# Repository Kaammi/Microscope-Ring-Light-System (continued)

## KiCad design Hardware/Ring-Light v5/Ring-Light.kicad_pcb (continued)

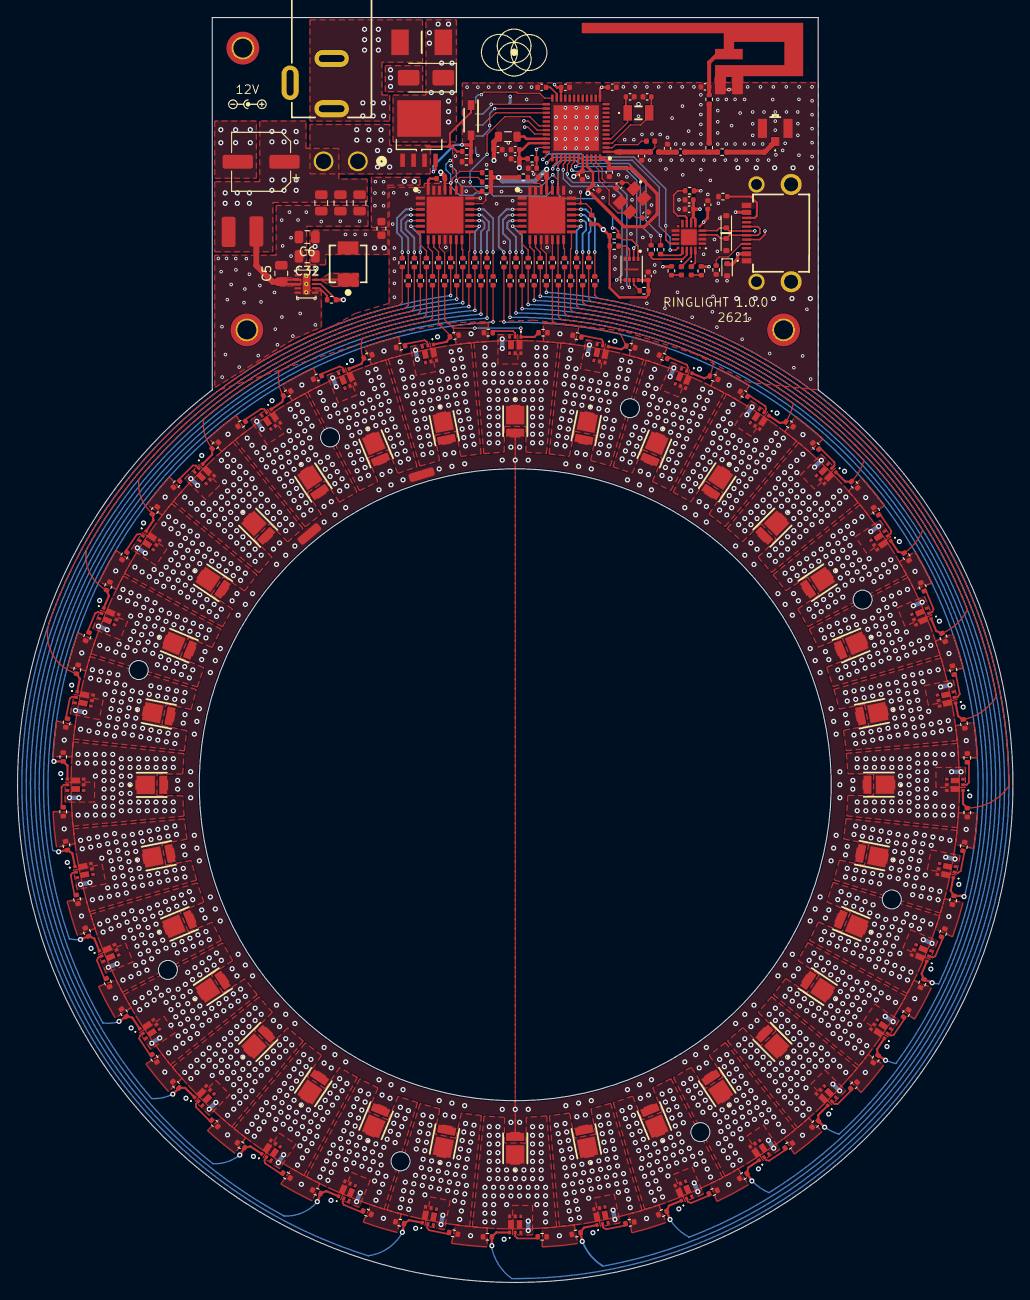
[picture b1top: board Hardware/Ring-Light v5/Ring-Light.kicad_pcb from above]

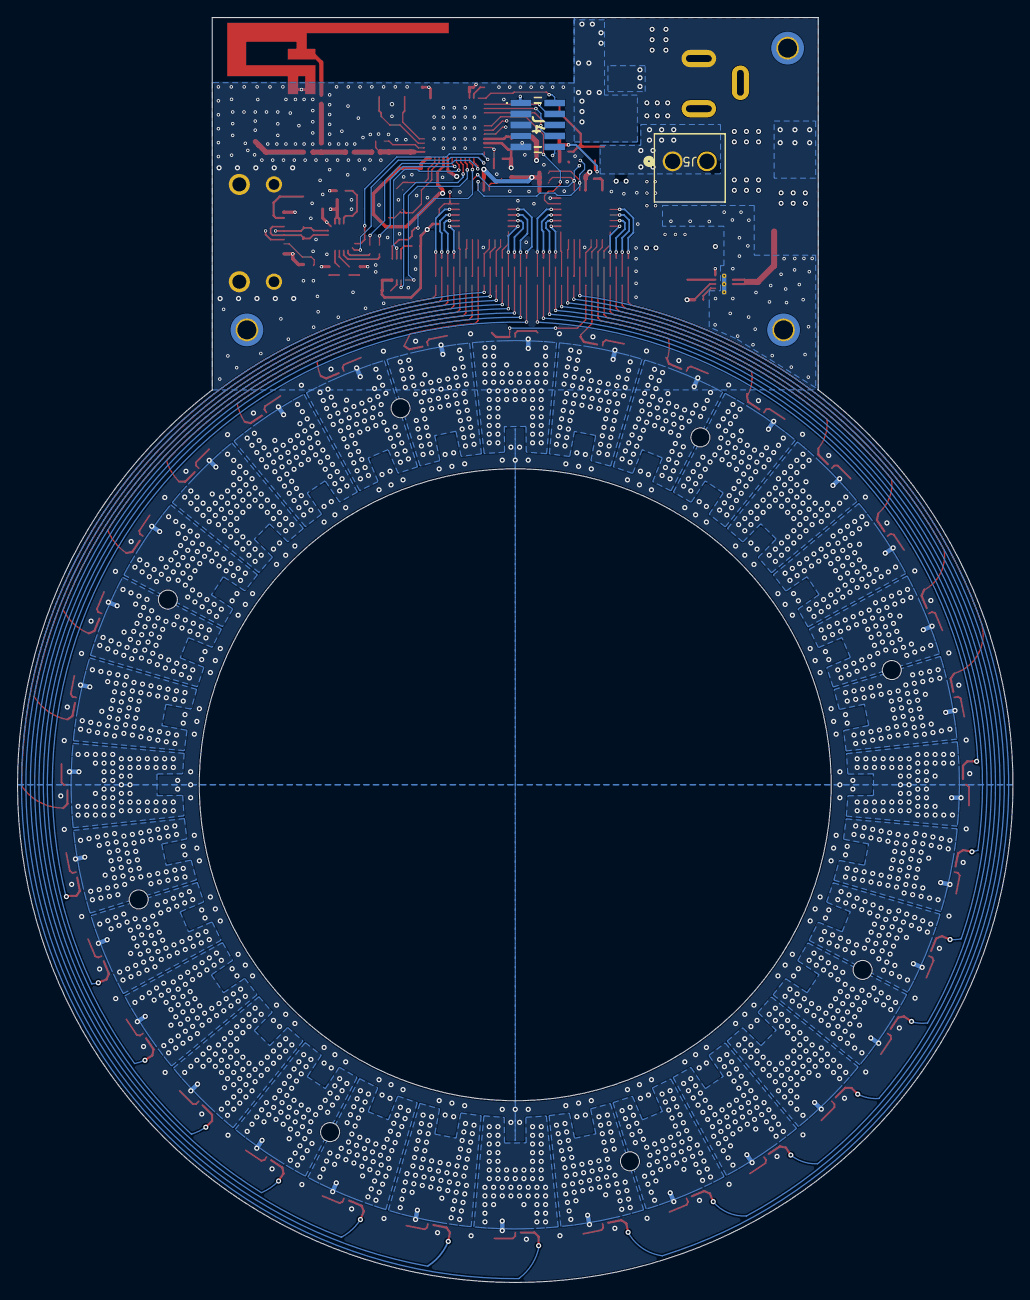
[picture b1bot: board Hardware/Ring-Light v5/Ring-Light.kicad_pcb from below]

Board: 4 copper layers, 115.0 x 146.1 mm, 252 parts (2 on the bottom side), 184 nets.

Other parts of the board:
MH1, MH2, MH3, MH4, MH5, MH5#2, MH6, MH7: MountingHole_2.2mm_M2

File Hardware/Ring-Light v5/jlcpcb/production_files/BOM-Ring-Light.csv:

Comment,Designator,Footprint,LCSC,Quantity
0,"R105,R106,R112,R113",R_0402_1005Metric,C17168,4
1.2pF,"C14,C27",C_0402_1005Metric,C72135,2
100,"R66,R67,R68,R69,R70,R71,R72,R73,R74,R75,R76,R77,R78,R79,R80,R81,R83,R84,R85,R86,R87,R88,R89,R90,R91,R92,R93,R94,R95,R96,R97,R98",R_0402_1005Metric,C25076,32
100k,"R1,R104,R11,R116,R117,R13,R15,R17,R19,R21,R23,R25,R27,R29,R3,R31,R33,R35,R37,R39,R41,R43,R45,R47,R49,R5,R51,R53,R55,R57,R59,R61,R63,R7,R9,R99",R_0402_1005Metric,C25741,36
100nF,"C1,C10,C12,C13,C15,C16,C17,C19,C2,C31,C7,C8",C_0402_1005Metric,C307331,12
1017457000B11LF,J2,1017457000B11LF,C22466645,1
10k,"R101,R108,R109,R118,R119,R65,R82",R_0402_1005Metric,C25744,7
10uF,"C11,C18",C_0402_1005Metric,C15525,2
10uF,C9,C_0805_2012Metric,C15850,1
10uH,L2,L_0805_2012Metric,C1046,1
12pF,"C22,C24,C25,C28,C29",C_0402_1005Metric,C1547,5
1k,"R100,R102,R103,R107,R114",R_0402_1005Metric,C11702,5
1uF,C30,C_0805_2012Metric,C28323,1
1uF,"C20,C21",C_0402_1005Metric,C52923,2
2.2k,R110,R_0402_1005Metric,C25879,1
2.2uF,C5,C_0805_2012Metric,C377773,1
2002112100010C4LF,J4,2002112100010C4LF,C150517,1
22uF,"C32,C6",C_0805_2012Metric,C45783,2
24MHz,Y2,TSX-3225,C2650460,1
32.768kHz,Y1,FC135327680KAAG0,C7275970,1
4.7uF,C26,C_0805_2012Metric,C1779,1
640445-2,J5,CONN2_640445-2_TEC,C86497,1
9.09,"R10,R12,R14,R16,R18,R2,R20,R22,R24,R26,R28,R30,R32,R34,R36,R38,R4,R40,R42,R44,R46,R48,R50,R52,R54,R56,R58,R6,R60,R62,R64,R8",R_0402_1005Metric,C166420,32
BLM18HE152SN1,FL1,L_0603_1608Metric,C82155,1
CP2102N-A02-GQFN20R,U37,CP2102NA02GQFN20,C969913,1
LED,"D1,D10,D11,D12,D13,D14,D15,D16,D17,D18,D19,D2,D20,D21,D22,D23,D24,D25,D26,D27,D28,D29,D3,D30,D31,D32,D4,D5,D6,D7,D8,D9",GWJTLRS1EMLVL5XX531,C2830571,32
MMSZ5242BT1G,D39,SOD3716X135N,C82050,1
NCR321PASX,"U1,U10,U11,U12,U13,U14,U15,U16,U17,U18,U19,U2,U20,U21,U22,U23,U24,U25,U26,U27,U28,U29,U3,U30,U31,U32,U4,U5,U6,U7,U8,U9",NCR321PASX,C3190647,32
"PCA9685BS,118","U33,U34",QFN65P600X600X100-29N-D,C5191634,2
SMAJ15A,D38,D_SMA,C132950,1
SQJ415EP-T1_GE3,Q1,SOT_SQJ415EP_VIS,C6495662,1
TPD1E10B06DPYR,"D33,D34,D35",D_SOD-523,C48260,3
TPS62177DQC,U36,WSON-10-1EP_2x3mm_P0.5mm_EP0.84x2.4mm_ThermalVias,C91241,1
U.FL-R-SMT-1_80,J3,UFLRSMT180,C88374,1
VLMY1500-GS08,"D36,D37",LED_0402_1005Metric,C511605,2
W25X40CLUXIG_TR,U38,PSON50P300X200X60-9N,C401661,1
100uF,C3,CP_Elec_6.3x7.7,,1
Fuse,F1,FUSC6127X294N,,1
694106301002,J1,694106301002,,1
Conn_01x01,J6,,,1
Conn_01x01,J7,,,1
Conn_01x01,J8,,,1
Conn_01x01,J9,,,1
10uH,L1,WE-LHMI_4020,,1
2nH,L3,L_0402_1005Metric,,1
15nH,L7,L_0402_1005Metric,,1
pad,REF**,pad,,1

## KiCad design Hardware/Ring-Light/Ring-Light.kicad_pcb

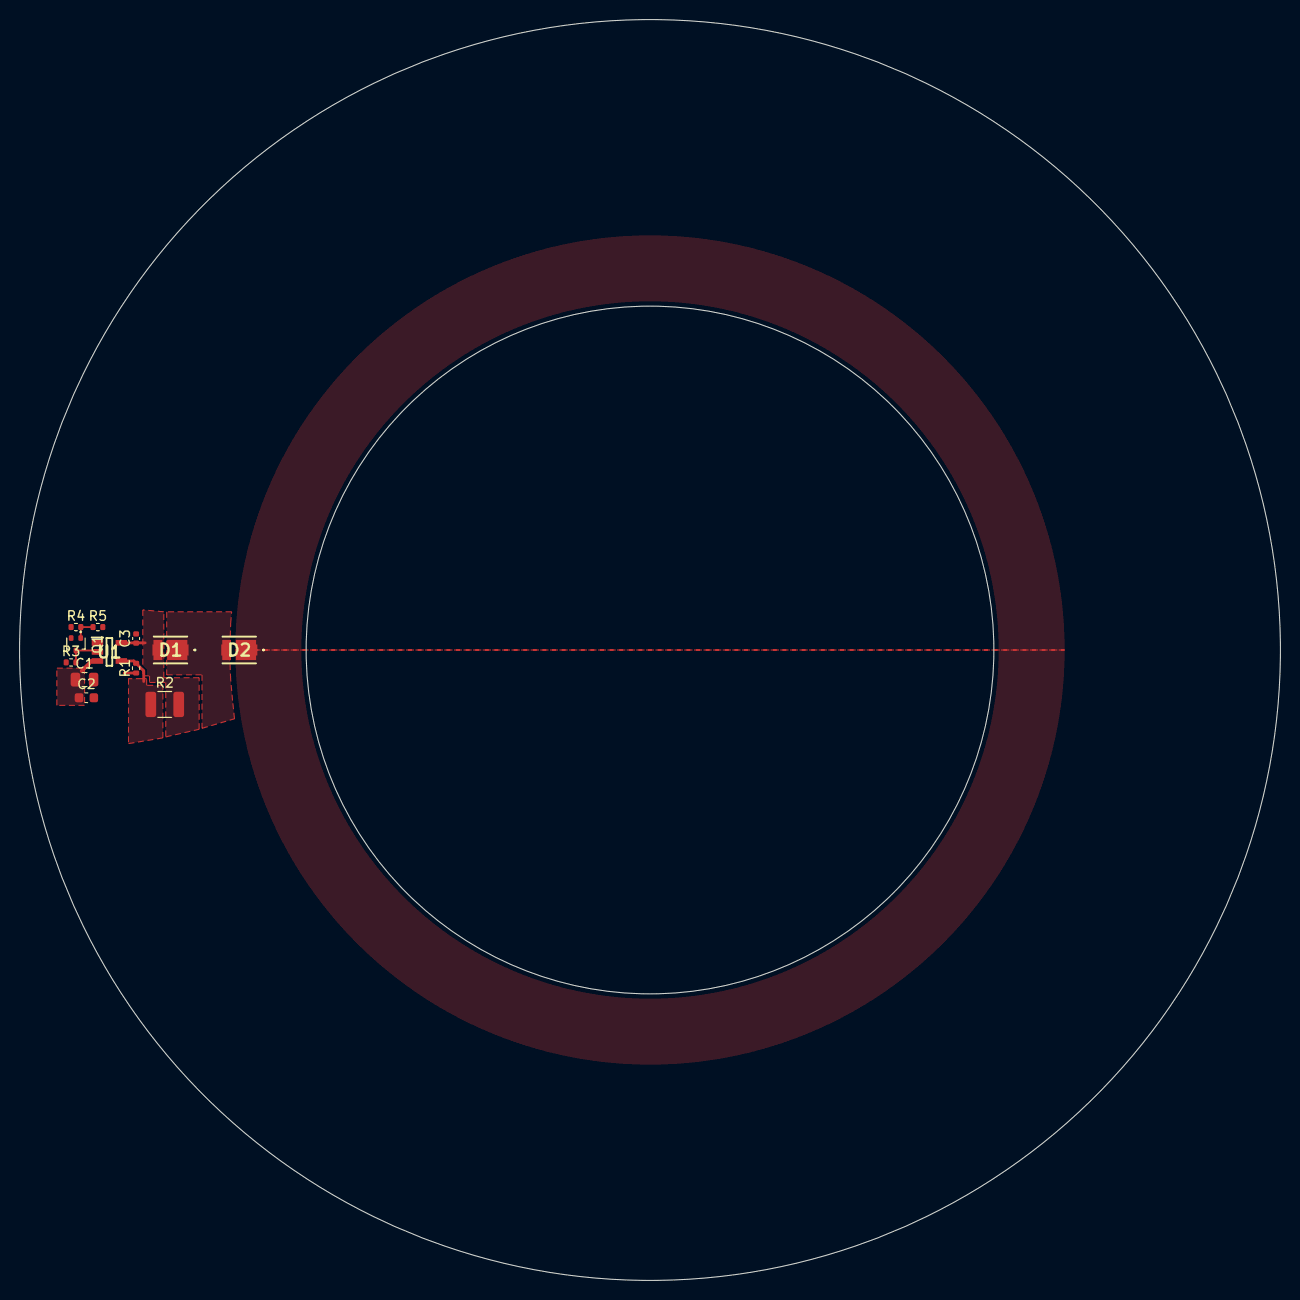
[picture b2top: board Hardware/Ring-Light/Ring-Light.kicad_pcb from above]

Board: 4 copper layers, 132.0 x 132.0 mm, 12 parts (0 on the bottom side), 7 nets.

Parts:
C1: 1uF; C_0805_2012Metric
C2: 0.1uF; C_0603_1608Metric
C3: 10nF; C_0402_1005Metric
D1, D2: LED; GWJTLRS1EMLVL5XX531
Q1: MMBT3904; SOT-416
R1: 1; R_0402_1005Metric
R2: 80.6; R_1210_3225Metric
R3: 1k; R_0402_1005Metric
R4, R5: 10k; R_0402_1005Metric
U1: TPS92612QDBVRQ1; SOT95P280X145-5N

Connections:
+12V: C1.1, C2.1, R1.1, U1.3 (SUPPLY)
/B1: Q1.1 (B), R4.2, R5.1
/IN1: R1.2, R2.1, U1.4 (IN)
/LED1: D1.1 (K), D1.2 (K), D2.3 (A), D2.4 (A)
/OUT1: C3.1, D1.3 (A), D1.4 (A), R2.2, U1.5 (OUT)
/PWM1: Q1.3 (C), R3.2, U1.2 (PWM)
GND: C1.2, C2.2, C3.2, D2.1 (K), D2.2 (K), Q1.2 (E), R5.2, U1.1 (GND)

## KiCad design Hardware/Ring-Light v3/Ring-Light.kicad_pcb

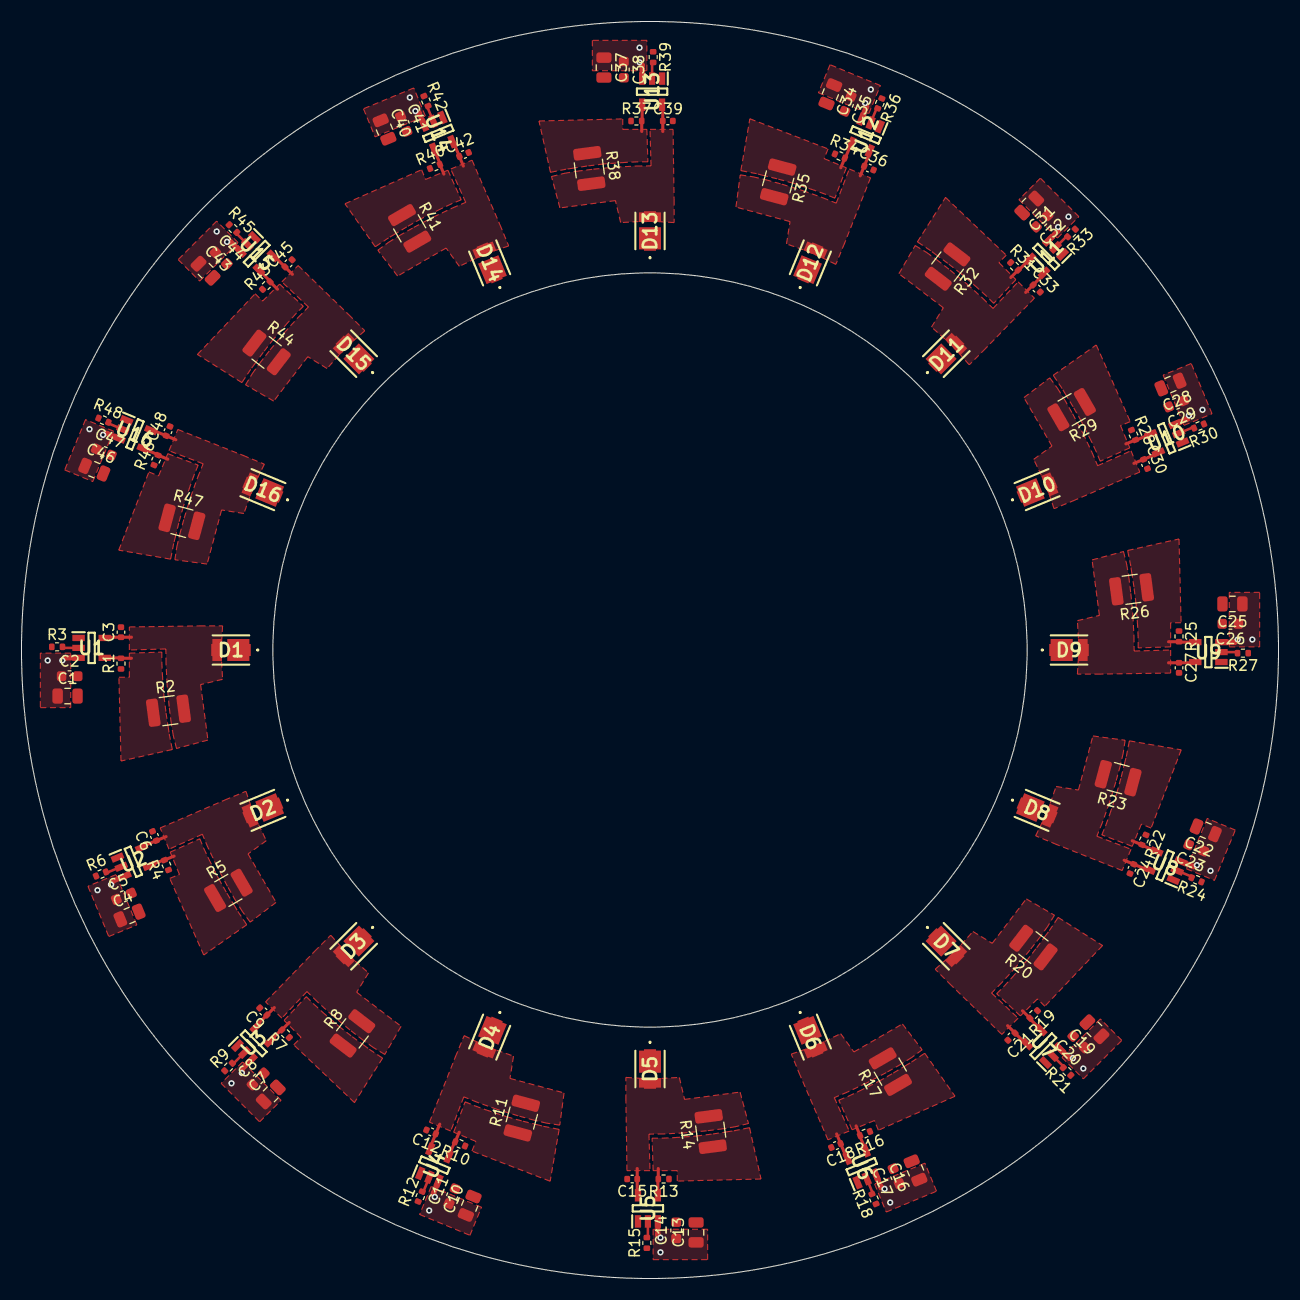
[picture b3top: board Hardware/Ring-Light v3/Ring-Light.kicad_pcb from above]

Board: 4 copper layers, 120.0 x 120.0 mm, 128 parts (0 on the bottom side), 6 nets.

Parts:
C1, C4, C7, C10, C13, C16, C19, C22, C25, C28, C31, C34, C37, C40, C43, C46: 1uF; C_0805_2012Metric
C2, C5, C8, C11, C14, C17, C20, C23, C26, C29, C32, C35, C38, C41, C44, C47: 0.1uF; C_0603_1608Metric
C3, C6, C9, C12, C15, C18, C21, C24, C27, C30, C33, C36, C39, C42, C45, C48: 10nF; C_0402_1005Metric
D1, D2, D3, D4, D5, D6, D7, D8, D9, D10, D11, D12, D13, D14, D15, D16: LED; GWJTLRS1EMLVL5XX531
R1, R4, R7, R10, R13, R16, R19, R22, R25, R28, R31, R34, R37, R40, R43, R46: 1; R_0402_1005Metric
R2, R5, R8, R11, R14, R17, R20, R23, R26, R29, R32, R35, R38, R41, R44, R47: 80.6; R_1210_3225Metric
R3, R6, R9, R12, R15, R18, R21, R24, R27, R30, R33, R36, R39, R42, R45, R48: 1k; R_0402_1005Metric
U1, U2, U3, U4, U5, U6, U7, U8, U9, U10, U11, U12, U13, U14, U15, U16: TPS92612QDBVRQ1; SOT95P280X145-5N

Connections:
+12V: C1.1, C2.1, C4.1, C5.1, C7.1, C8.1, C10.1, C11.1, C13.1, C14.1, C16.1, C17.1, C19.1, C20.1, C22.1, C23.1, C25.1, C26.1, C28.1, C29.1, C31.1, C32.1, C34.1, C35.1, C37.1, C38.1, C40.1, C41.1, C43.1, C44.1, C46.1, C47.1, R1.1, R4.1, R7.1, R10.1, R13.1, R16.1, R19.1, R22.1, R25.1, R28.1, R31.1, R34.1, R37.1, R40.1, R43.1, R46.1, U1.3 (SUPPLY), U2.3 (SUPPLY), U3.3 (SUPPLY), U4.3 (SUPPLY), U5.3 (SUPPLY), U6.3 (SUPPLY), U7.3 (SUPPLY), U8.3 (SUPPLY), U9.3 (SUPPLY), U10.3 (SUPPLY), U11.3 (SUPPLY), U12.3 (SUPPLY), U13.3 (SUPPLY), U14.3 (SUPPLY), U15.3 (SUPPLY), U16.3 (SUPPLY)
/IN1: R1.2, R2.1, R4.2, R5.1, R7.2, R8.1, R10.2, R11.1, R13.2, R14.1, R16.2, R17.1, R19.2, R20.1, R22.2, R23.1, R25.2, R26.1, R28.2, R29.1, R31.2, R32.1, R34.2, R35.1, R37.2, R38.1, R40.2, R41.1, R43.2, R44.1, R46.2, R47.1, U1.4 (IN), U2.4 (IN), U3.4 (IN), U4.4 (IN), U5.4 (IN), U6.4 (IN), U7.4 (IN), U8.4 (IN), U9.4 (IN), U10.4 (IN), U11.4 (IN), U12.4 (IN), U13.4 (IN), U14.4 (IN), U15.4 (IN), U16.4 (IN)
/OUT1: C3.1, C6.1, C9.1, C12.1, C15.1, C18.1, C21.1, C24.1, C27.1, C30.1, C33.1, C36.1, C39.1, C42.1, C45.1, C48.1, D1.3 (A), D1.4 (A), D2.3 (A), D2.4 (A), D3.3 (A), D3.4 (A), D4.3 (A), D4.4 (A), D5.3 (A), D5.4 (A), D6.3 (A), D6.4 (A), D7.3 (A), D7.4 (A), D8.3 (A), D8.4 (A), D9.3 (A), D9.4 (A), D10.3 (A), D10.4 (A), D11.3 (A), D11.4 (A), D12.3 (A), D12.4 (A), D13.3 (A), D13.4 (A), D14.3 (A), D14.4 (A), D15.3 (A), D15.4 (A), D16.3 (A), D16.4 (A), R2.2, R5.2, R8.2, R11.2, R14.2, R17.2, R20.2, R23.2, R26.2, R29.2, R32.2, R35.2, R38.2, R41.2, R44.2, R47.2, U1.5 (OUT), U2.5 (OUT), U3.5 (OUT), U4.5 (OUT), U5.5 (OUT), U6.5 (OUT), U7.5 (OUT), U8.5 (OUT), U9.5 (OUT), U10.5 (OUT), U11.5 (OUT), U12.5 (OUT), U13.5 (OUT), U14.5 (OUT), U15.5 (OUT), U16.5 (OUT)
/PWM1: R3.2, R6.2, R9.2, R12.2, R15.2, R18.2, R21.2, R24.2, R27.2, R30.2, R33.2, R36.2, R39.2, R42.2, R45.2, R48.2, U1.2 (PWM), U2.2 (PWM), U3.2 (PWM), U4.2 (PWM), U5.2 (PWM), U6.2 (PWM), U7.2 (PWM), U8.2 (PWM), U9.2 (PWM), U10.2 (PWM), U11.2 (PWM), U12.2 (PWM), U13.2 (PWM), U14.2 (PWM), U15.2 (PWM), U16.2 (PWM)
GND: C1.2, C2.2, C3.2, C4.2, C5.2, C6.2, C7.2, C8.2, C9.2, C10.2, C11.2, C12.2, C13.2, C14.2, C15.2, C16.2, C17.2, C18.2, C19.2, C20.2, C21.2, C22.2, C23.2, C24.2, C25.2, C26.2, C27.2, C28.2, C29.2, C30.2, C31.2, C32.2, C33.2, C34.2, C35.2, C36.2, C37.2, C38.2, C39.2, C40.2, C41.2, C42.2, C43.2, C44.2, C45.2, C46.2, C47.2, C48.2, D1.1 (K), D1.2 (K), D2.1 (K), D2.2 (K), D3.1 (K), D3.2 (K), D4.1 (K), D4.2 (K), D5.1 (K), D5.2 (K), D6.1 (K), D6.2 (K), D7.1 (K), D7.2 (K), D8.1 (K), D8.2 (K), D9.1 (K), D9.2 (K), D10.1 (K), D10.2 (K), D11.1 (K), D11.2 (K), D12.1 (K), D12.2 (K), D13.1 (K), D13.2 (K), D14.1 (K), D14.2 (K), D15.1 (K), D15.2 (K), D16.1 (K), D16.2 (K), U1.1 (GND), U2.1 (GND), U3.1 (GND), U4.1 (GND), U5.1 (GND), U6.1 (GND), U7.1 (GND), U8.1 (GND), U9.1 (GND), U10.1 (GND), U11.1 (GND), U12.1 (GND), U13.1 (GND), U14.1 (GND), U15.1 (GND), U16.1 (GND)
PWM: R3.1, R6.1, R9.1, R12.1, R15.1, R18.1, R21.1, R24.1, R27.1, R30.1, R33.1, R36.1, R39.1, R42.1, R45.1, R48.1
